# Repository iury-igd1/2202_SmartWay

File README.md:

<p align="center">
  Orientação por voz e vibração para viagens de ônibus.<br>
  Um projeto do <strong>Grupo 2202</strong>, desenvolvido para a <strong>PROJETE 2025</strong>.
</p>

<p align="center">

</p>

<p align="center">
  <a href="#projeto">Conheça o projeto</a> ·
  <a href="#fluxo">Acompanhe a viagem</a> ·
  <a href="#arquitetura">Entenda a arquitetura</a> ·
  <a href="#execucao">Execute o protótipo</a> ·
  <a href="#arquivos">Explore os arquivos</a> ·
</p>

---

## O ônibus certo, no momento certo

Em um ponto movimentado, identificar o ônibus que se aproxima e saber quando descer pode depender de ajuda de outras pessoas. O **SmartWay** foi criado para orientar pessoas com deficiência visual nesses momentos por meio de uma pulseira com **um botão, mensagens de áudio e padrões de vibração**.

O usuário informa origem e destino por voz. Durante a viagem, a pulseira recebe do servidor o estado do trajeto e avisa quando o ônibus se aproxima do embarque ou do desembarque. Um simulador em mapa fornece as posições dos ônibus usadas nesta versão do projeto.

| Pergunta durante a viagem | Resposta do protótipo |
| --- | --- |
| **“Como informo para onde quero ir?”** | Segure o botão e fale a origem; repita para o destino. |
| **“Qual ônibus devo esperar?”** | O servidor procura uma linha que passe pelos dois pontos na ordem correta e associa um ônibus simulado à viagem. |
| **“Quando preciso me preparar?”** | Áudio e vibração sinalizam a aproximação do ônibus e do destino. |
| **“Como encerro a viagem?”** | Um clique duplo solicita o cancelamento. |

## Da fala ao aviso

1. **Iniciar.** Um clique único solicita uma nova viagem. A bateria é lida nesse momento; tensão de 3,3 V ou menos gera aviso, sem bloquear o início.
2. **Definir.** Ao segurar o botão, a pulseira grava até quatro segundos de áudio e envia um WAV ao servidor. O processo se repete para origem e destino.
3. **Encontrar a rota.** O servidor transcreve a fala com Whisper, procura os nomes e apelidos das paradas e seleciona uma linha válida.
4. **Acompanhar.** O simulador publica as posições dos ônibus. O servidor calcula distância e ETA; a pulseira consulta o estado a cada dois segundos.
5. **Avisar.** Faixas de áudio e pulsos de vibração marcam a aproximação, o embarque, o percurso e a chegada.

O clique longo grava a voz, o clique único inicia e o duplo cancela. A [tabela de gestos e faixas](firmware/README.md) mostra os tempos e os avisos implementados.

## Três partes, uma viagem

```mermaid
flowchart LR
    P["Pulseira ESP32<br/>botão, voz e vibração"] -->|"WAV e comandos HTTP"| A["Servidor Python<br/>API e estado da viagem"]
    A -->|"estado, distância e ETA"| P
    S["Simulador no navegador<br/>mapa e ônibus"] -->|"posições dos ônibus"| A
    A -->|"viagem atual"| S
    D["Rotas e paradas<br/>arquivos JSON"] --> A
    D --> S
```

| Parte | Papel | Onde ler mais |
| --- | --- | --- |
| **Pulseira** | Lê o botão e o microfone I2S; reproduz áudio pelo DFPlayer Mini e aciona o motor de vibração. | [Firmware](firmware/README.md) |
| **Servidor** | Transcreve a voz, identifica paradas, calcula rota e ETA e mantém o estado da viagem em memória. | [Software](software/README.md) |
| **Simulador** | Desenha quatro linhas no mapa, move ônibus e envia as posições ao servidor. | [Software](software/README.md) |
| **Placa e case** | Layout da PCB, esquemático documental alinhado a ela e duas peças STL da caixa. | [Hardware](hardware/README.md) |

**O rastreamento desta versão vem do simulador.** Não há integração com GPS ou dados de uma frota real. O servidor mantém a viagem somente em memória, e reiniciá-lo encerra o acompanhamento em curso.

## Execute o protótipo

Os comandos abaixo são para **PowerShell no Windows**. O servidor espera encontrar os JSONs no diretório atual, por isso deve ser iniciado de dentro de `software/`.

### 1. Prepare o Python

Use Python 3.11, instale FFmpeg no sistema e confirme que o comando `ffmpeg` está disponível no terminal.

```powershell
py -3.11 -m venv .venv
.\.venv\Scripts\python.exe -m pip install -r .\software\requirements.txt
```

### 2. Inicie o servidor

```powershell
cd .\software
..\.venv\Scripts\python.exe .\servidor.py
```

O servidor carrega o modelo Whisper `small` e atende na porta **5000**. A primeira carga do modelo pode exigir download.

### 3. Sirva o simulador

Em outro terminal, na **raiz do repositório**:

```powershell
.\.venv\Scripts\python.exe -m http.server 8000 --directory .\software
```

Abra `http://localhost:8000/simulador.html` e inicie a simulação. O HTML precisa ser servido por HTTP para carregar os três JSONs locais.

### 4. Conecte a pulseira

O firmware depende de uma placa ESP32 compatível, microfone I2S, DFPlayer Mini com cartão SD, botão, LED e motor de vibração. Instale o suporte ESP32 no Arduino IDE e as bibliotecas **ArduinoJson** e **DFRobotDFPlayerMini**. Os arquivos MP3 das quinze mensagens não estão disponíveis neste repositório, mas podem ser gravados manualmente.

O firmware e o simulador contêm um IP fixo do servidor, e o firmware também contém as credenciais da rede usada no protótipo. Esses valores precisam corresponder à rede da demonstração. Veja os [pinos e dependências](firmware/README.md) e os [detalhes do servidor](software/README.md).

## Explore os arquivos

| Pasta ou arquivo | Conteúdo |
| --- | --- |
| [`firmware/`](firmware/README.md) | Código Arduino da pulseira e guia de operação. |
| [`software/`](software/README.md) | API, simulador, dados de rotas e dependências Python. |
| [`hardware/`](hardware/README.md) | Layout EAGLE, esquemático corrigido e peças STL do case. |
| [`docs/GUIA_DO_CODIGO.md`](docs/GUIA_DO_CODIGO.md) | Funções, estados e rotas HTTP em detalhe. |
| [Diário de bordo](https://eteacojeorg-my.sharepoint.com/:o:/g/personal/iury_souza_edu_etefmc_com_br/IgDuZ5tOZYT5RrS-5chnWQInAXWTRA5idvHaHn-ZRV22YVc) | Registro externo do desenvolvimento do projeto. |
| [`LICENSE`](LICENSE) | Condições proprietárias de uso. |

### Publicação e licença

O código e os materiais próprios do projeto estão sob [licença proprietária](LICENSE). Bibliotecas e imagens externas mantêm as condições de seus titulares.

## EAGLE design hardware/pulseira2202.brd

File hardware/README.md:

# Placa e case da pulseira

Esta pasta registra o hardware do SmartWay: o layout de uma PCB já produzida, um esquemático reconstruído para documentá-la e as duas malhas STL da caixa. O [firmware](../firmware/README.md) usa os pinos descritos abaixo.

Volte à [visão geral do SmartWay](../README.md).

## Arquivos disponíveis

| Arquivo | Conteúdo |
| --- | --- |
| [`pulseira2202.brd`](pulseira2202.brd) | Layout da PCB em XML do Autodesk EAGLE 9.7.0. |
| [`pulseira2202.sch`](pulseira2202.sch) | Esquemático EAGLE corrigido depois, a partir do layout. |
| [`pulseira_2202_base.stl`](pulseira_2202_base.stl) | Peça chamada base do case. |
| [`pulseira_2202_topo.stl`](pulseira_2202_topo.stl) | Peça chamada topo do case. |

O `.brd` é o desenho físico da placa; o `.sch` representa símbolos e ligações elétricas.

## O que a placa reúne

O contorno da PCB mede **51,75 × 44,762 mm**. O layout contém **17 componentes e conectores**, trilhas nas camadas superior e inferior e vias entre elas.

| Conjunto | Elementos encontrados |
| --- | --- |
| Controle e voz | ESP32 C3 SuperMini (`U$4`) e microfone INMP441 (`U$2`). |
| Áudio | DFPlayer (`U$1`) e conector `JACKP2` para saída de alto-falante. |
| Interação | Botão `S1` e LED `LED1`. |
| Vibração | Conector `VIBRA`, transistor `Q2`, diodo `D1` e resistor `R7` de 1 kΩ. |
| Alimentação e bateria | Regulador HT7833 (`IC1`), capacitor `C1`, conectores de alimentação e divisor `R1`/`R2` de 100 kΩ cada. |

Os sinais do layout correspondem aos GPIOs usados no firmware: **0** para bateria, **2** para vibração, **3** para botão, **4/5/6** para I2S, **8/9** para DFPlayer e **10** para LED. O divisor de dois resistores iguais explica o fator 2 aplicado à tensão lida em `checkBattery()`.

## As duas peças do case

Os STL são binários e não registram unidade. **Se exportados em milímetros**, suas caixas delimitadoras são:

| Peça | X × Y × Z |
| :--- | :---: |
| Base | 61,428 × 66 × 12,458 mm |
| Topo | 58,940 × 66 × 26,000 mm |

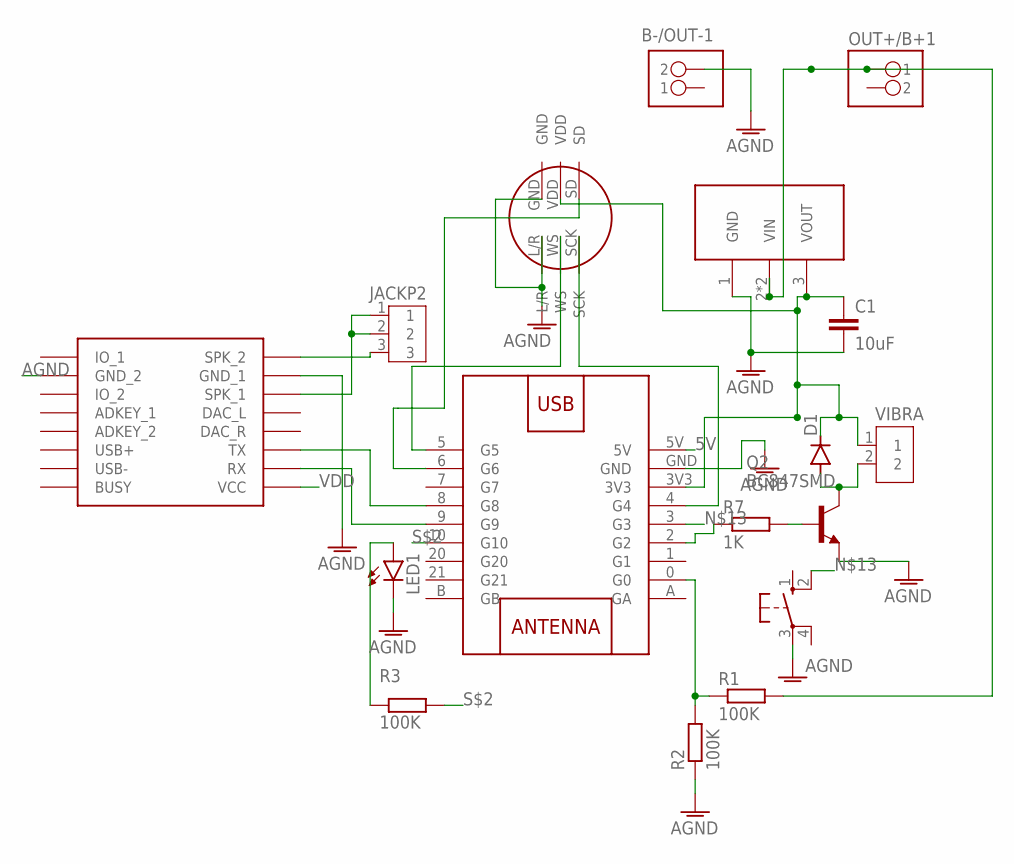
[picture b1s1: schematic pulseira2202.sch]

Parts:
B-/OUT-1: PINHD-1X02_1X02M; 1X02
C1: 10uF; C0805
D1: DIODE-SOD123; SOD123
IC1: HT7833; SOT89
JACKP2: B3B-XH-A
LED1: LED3MM
OUT+/B+1: PINHD-1X02_1X02M; 1X02
Q2: BC847SMD; SOT23
R1, R2, R3: 100K; R0805
R7: 1K; R0805
S1: 10-XX; B3F-10XX
U$1: DFPLAYER
U$2: INMP441_CIRCULAR; MIC_CIRCULAR
U$4: ESP32SUPERMINI_ESP32-SUPERMINI
VIBRA: B2B-XH-A

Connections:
5V: U$4.5V
AGND: B-/OUT-1.2, C1.2, IC1.1 (GND), LED1.K (C), Q2.2 (E), R2.1, S1.3, U$1.GND_1, U$1.GND_2, U$2.GND, U$2.L/R, U$4.GND
unnamed: U$1.RX, U$4.9 (G9)
unnamed: U$1.TX, U$4.8 (G8)
unnamed: JACKP2.1, JACKP2.2, U$1.SPK1 (SPK_1)
unnamed: JACKP2.3, U$1.SPK2 (SPK_2)
unnamed: Q2.1 (B), R7.2
unnamed: R7.1, U$4.2 (G2)
unnamed: D1.A, Q2.3 (C), VIBRA.2
unnamed: U$2.WS, U$4.5 (G5)
unnamed: U$2.SCK, U$4.4 (G4)
unnamed: U$2.SD, U$4.6 (G6)
unnamed: S1.2 (S1), U$4.3 (G3)
unnamed: IC1.2 (VIN), IC1.2@1 (VIN), OUT+/B+1.1, R1.2
unnamed: R1.1, R2.2, U$4.0 (G0)
S$1: LED1.A, R3.2
S$2: R3.1, U$4.10 (G10)
VDD: C1.1, D1.C, IC1.3 (VOUT), U$1.VCC, U$2.VDD, U$4.3V3, VIBRA.1

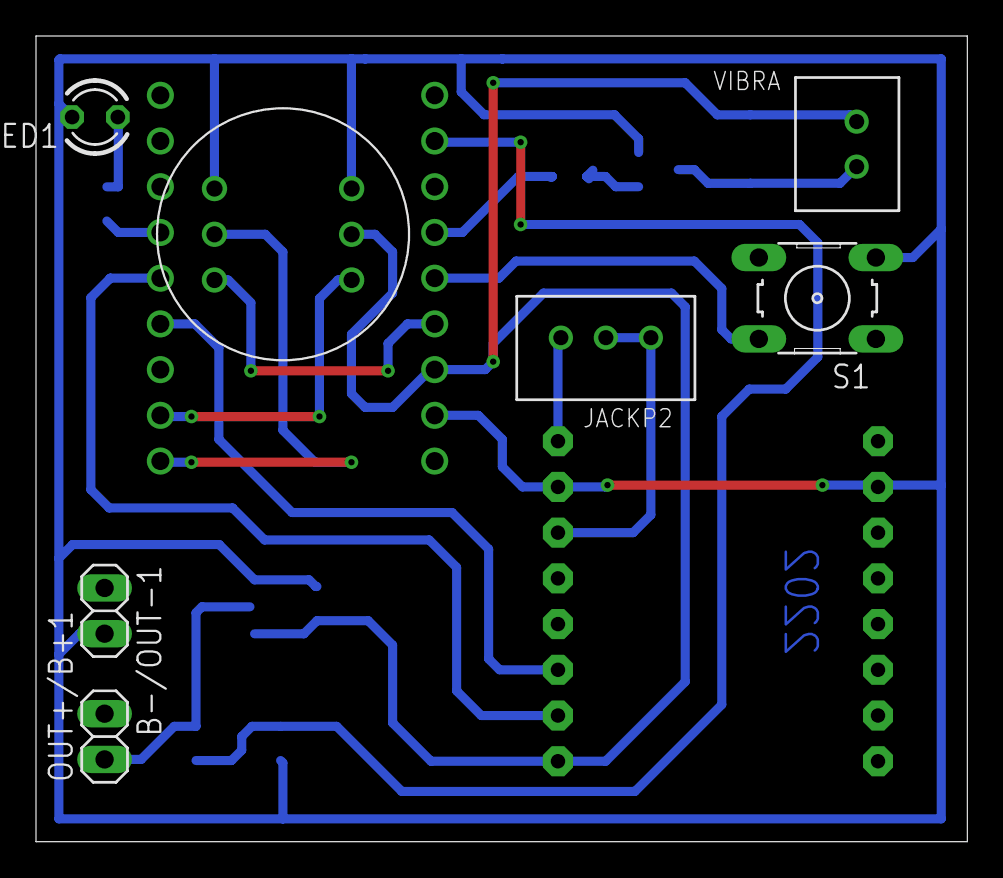
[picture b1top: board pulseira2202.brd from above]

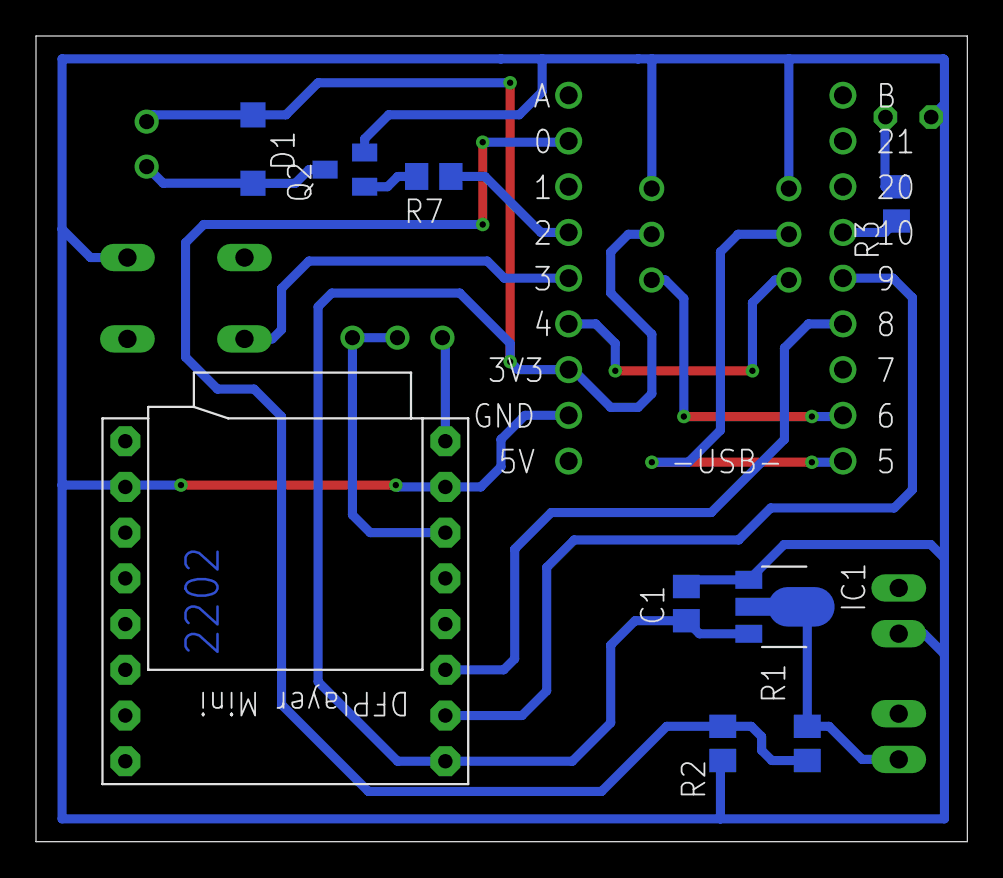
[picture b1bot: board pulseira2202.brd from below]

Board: 2 copper layers, 51.7 x 44.8 mm, 17 parts (10 on the bottom side), 17 nets.
